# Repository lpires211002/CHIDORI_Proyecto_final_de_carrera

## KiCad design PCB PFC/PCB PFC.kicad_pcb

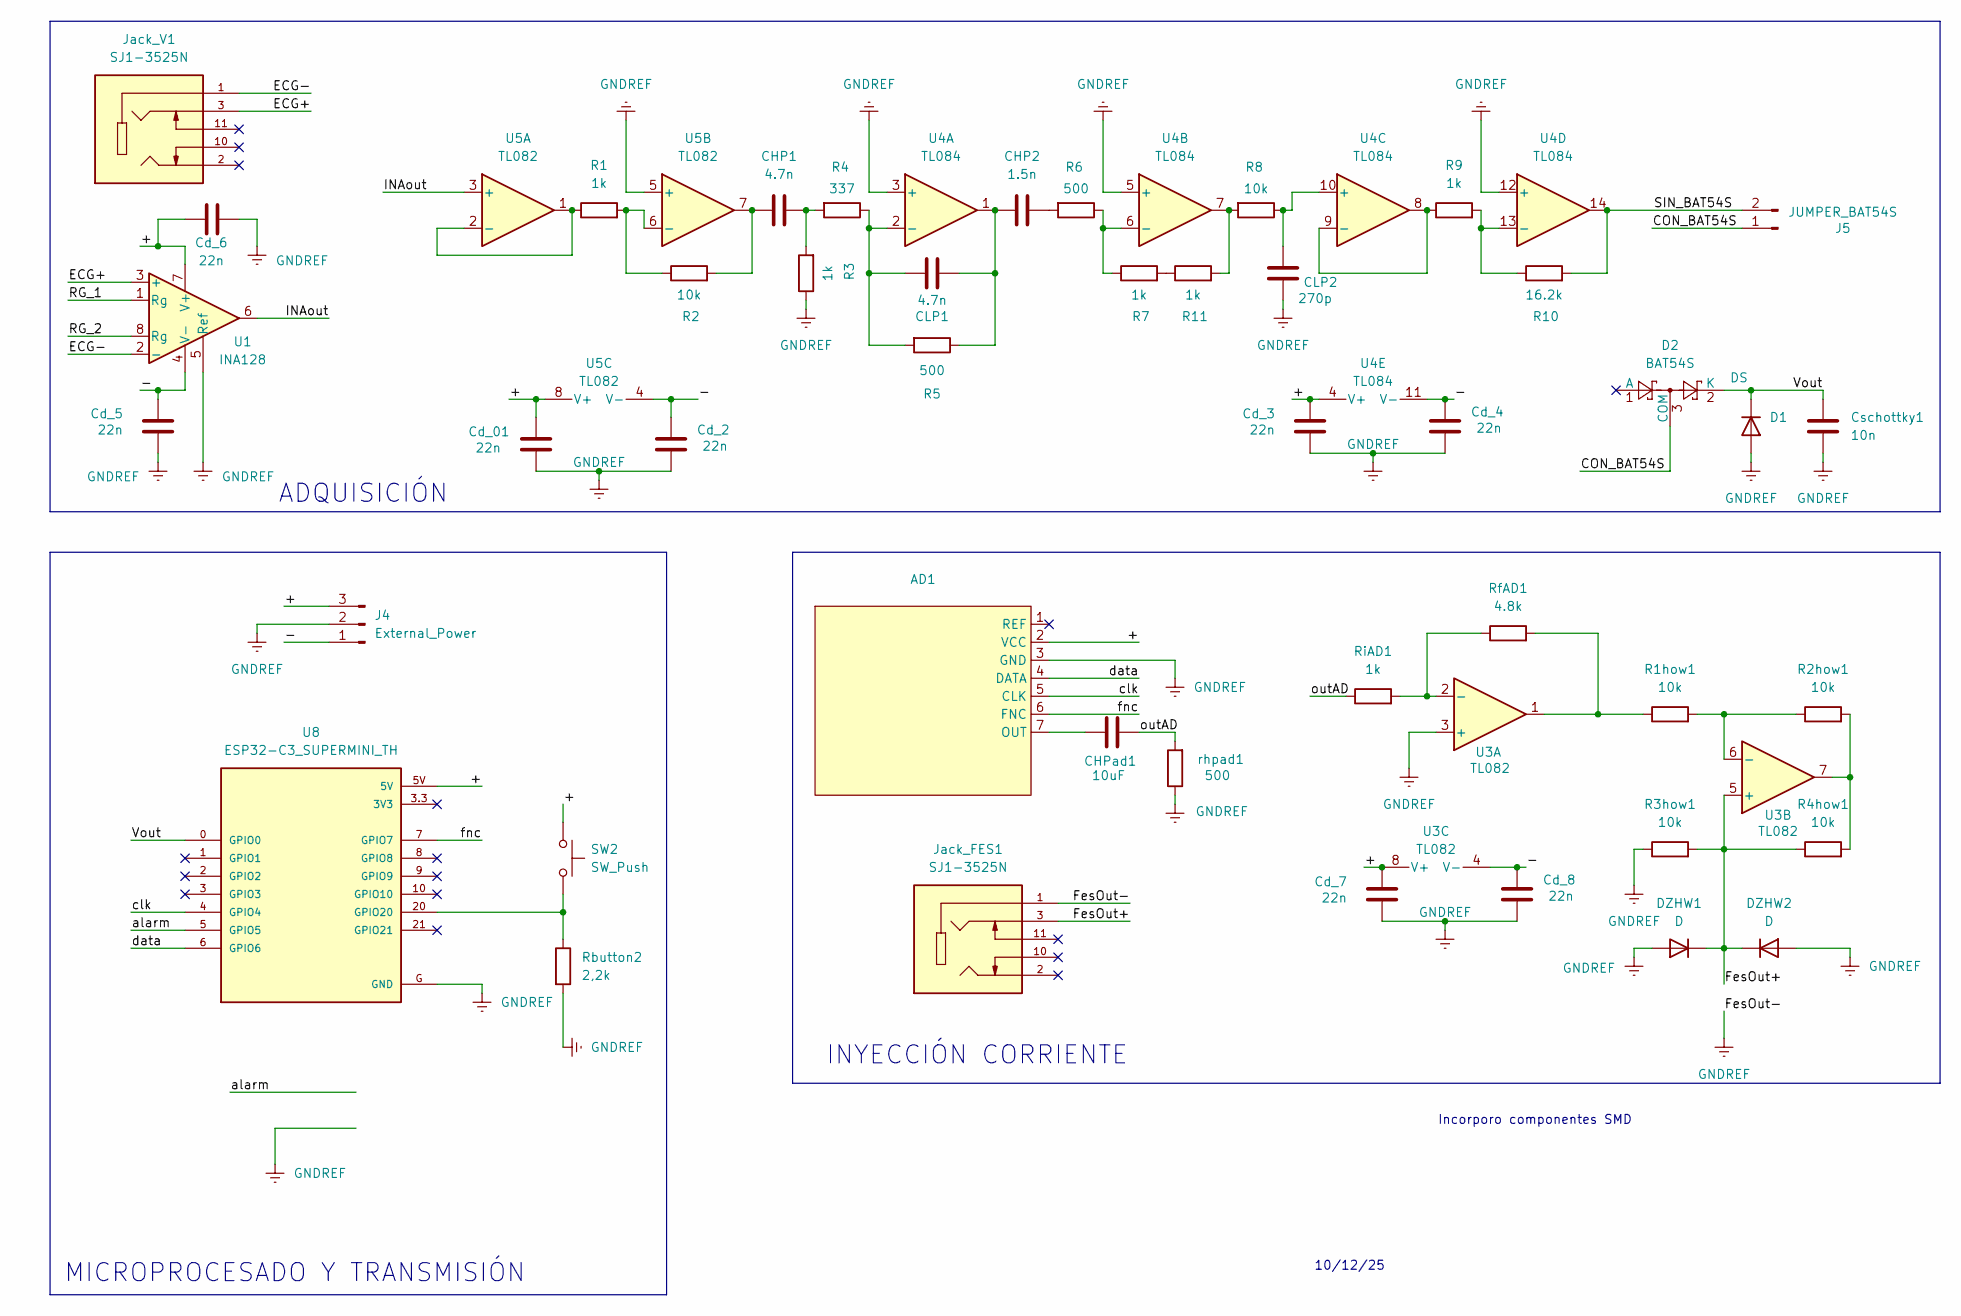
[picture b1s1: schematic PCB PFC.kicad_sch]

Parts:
AD1: AD9833
CHP1: 4.7n; C_0603_1608Metric
CHP2: 1.5n; C_0603_1608Metric
CHPad1: 10uF; C_0603_1608Metric
CLP1: 4.7n; C_0603_1608Metric
CLP2: 270p; C_0603_1608Metric
Cd_01, Cd_2, Cd_3, Cd_4, Cd_5, Cd_6, Cd_7, Cd_8: 22n; C_0603_1608Metric
Cschottky1: 10n; C_0603_1608Metric
D1: DS; D_DO-35_SOD27_P7.62mm_Horizontal
D2: BAT54S; SOT-23
DZHW1, DZHW2: D; D_DO-35_SOD27_P7.62mm_Horizontal
J4: External_Power; JST_EH_B3B-EH-A_1x03_P2.50mm_Vertical
J5: JUMPER_BAT54S; PinSocket_1x02_P2.54mm_Vertical
Jack_FES1: SJ1-3525N; CUI_SJ1-3525N; PARTREV 1.05
Jack_V1: SJ1-3525N; CUI_SJ1-3525N; PARTREV 1.05
R1, R3, R7, R9, R11: 1k; R_0805_2012Metric
R1how1, R2, R2how1, R3how1, R4how1, R8: 10k; R_0805_2012Metric
R4: 337; R_0805_2012Metric
R5, R6: 500; R_0805_2012Metric
R10: 16.2k; R_0805_2012Metric
Rbutton2: 2,2k; R_0805_2012Metric
RfAD1: 4.8k; R_0805_2012Metric
RiAD1: 1k; R_0805_2012Metric
SW2: SW_Push; SW_PUSH_6mm
U1: INA128; SOIC-8_3.9x4.9mm_P1.27mm
U3, U5: TL082; SOIC-8_3.9x4.9mm_P1.27mm
U4: TL084; SOIC-14_3.9x8.7mm_P1.27mm
U8: ESP32-C3_SUPERMINI_TH; MODULE_ESP32-C3_SUPERMINI_TH
rhpad1: 500; R_0805_2012Metric

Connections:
/+: AD1.2 (VCC), Cd_01.2, Cd_3.2, Cd_6.2, Cd_7.2, J4.3, SW2.1, U1.7 (V+), U3.8 (V+), U4.4 (V+), U5.8 (V+), U8.5V
/-: Cd_2.2, Cd_4.2, Cd_5.2, Cd_8.2, J4.1, U1.4 (V-), U3.4 (V-), U4.11 (V-), U5.4 (V-)
/CON_BAT54S: D2.3 (COM), J5.1
/ECG+: Jack_V1.3, U1.3 (+)
/ECG-: Jack_V1.1, U1.2 (-)
/FesOut+: DZHW1.1 (K), DZHW2.1 (K), Jack_FES1.3, R3how1.2, R4how1.1, U3.5 (+)
/INAout: U1.6, U5.3 (+)
/RG_1: U1.1 (Rg)
/RG_2: U1.8 (Rg)
/SIN_BAT54S: J5.2, R10.2, U4.14
/Vout: Cschottky1.2, D1.1 (K), D2.2 (K), U8.0 (GPIO0)
/alarm: U8.5 (GPIO5); also elsewhere on the board
/clk: AD1.5 (CLK), U8.4 (GPIO4)
/data: AD1.4 (DATA), U8.6 (GPIO6)
/fnc: AD1.6 (FNC), U8.7 (GPIO7)
/outAD: CHPad1.2, RiAD1.1, rhpad1.2
GNDREF: AD1.3 (GND), CLP2.1, Cd_01.1, Cd_2.1, Cd_3.1, Cd_4.1, Cd_5.1, Cd_6.1, Cd_7.1, Cd_8.1, Cschottky1.1, D1.2 (A), DZHW1.2 (A), DZHW2.2 (A), J4.2, Jack_FES1.1, R3.1, R3how1.1, Rbutton2.2, U1.5 (Ref), U3.3 (+), U4.3 (+), U4.5 (+), U4.12 (+), U5.5 (+), U8.G (GND), rhpad1.1; also elsewhere on the board
unnamed: AD1.7 (OUT), CHPad1.1
unnamed: CHP1.1, R2.2, U5.7
unnamed: CHP1.2, R3.2, R4.2
unnamed: CHP2.1, CLP1.2, R5.1, U4.1
unnamed: CHP2.2, R6.2
unnamed: R1how1.1, RfAD1.2, U3.1
unnamed: R2how1.2, R4how1.2, U3.7
unnamed: R7.2, R11.1
unnamed: R8.2, R11.2, U4.7
unnamed: RfAD1.1, RiAD1.2, U3.2 (-)
unnamed: R1how1.2, R2how1.1, U3.6 (-)
unnamed: CLP1.1, R4.1, R5.2, U4.2 (-)
unnamed: R6.1, R7.1, U4.6 (-)
unnamed: CLP2.2, R8.1, U4.10 (+)
unnamed: R9.1, U4.8, U4.9 (-)
unnamed: R9.2, R10.1, U4.13 (-)
unnamed: R1.1, U5.1, U5.2 (-)
unnamed: R1.2, R2.1, U5.6 (-)
unnamed: Rbutton2.1, SW2.2, U8.20 (GPIO20)

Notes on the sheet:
10/12/25
ADQUISICIÓN
Incorporo componentes SMD
MICROPROCESADO Y TRANSMISIÓN
INYECCIÓN CORRIENTE

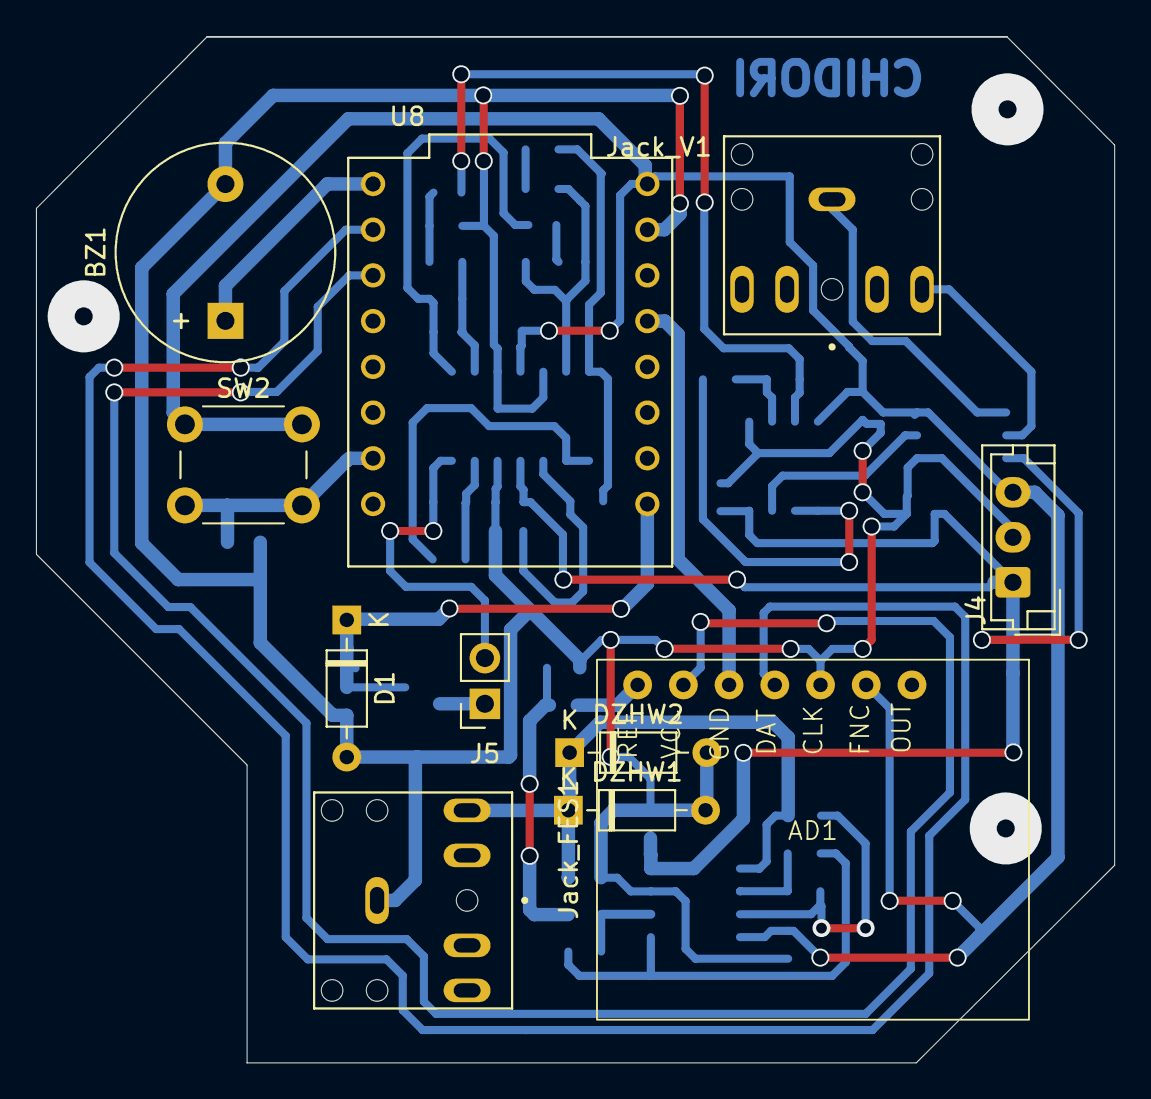
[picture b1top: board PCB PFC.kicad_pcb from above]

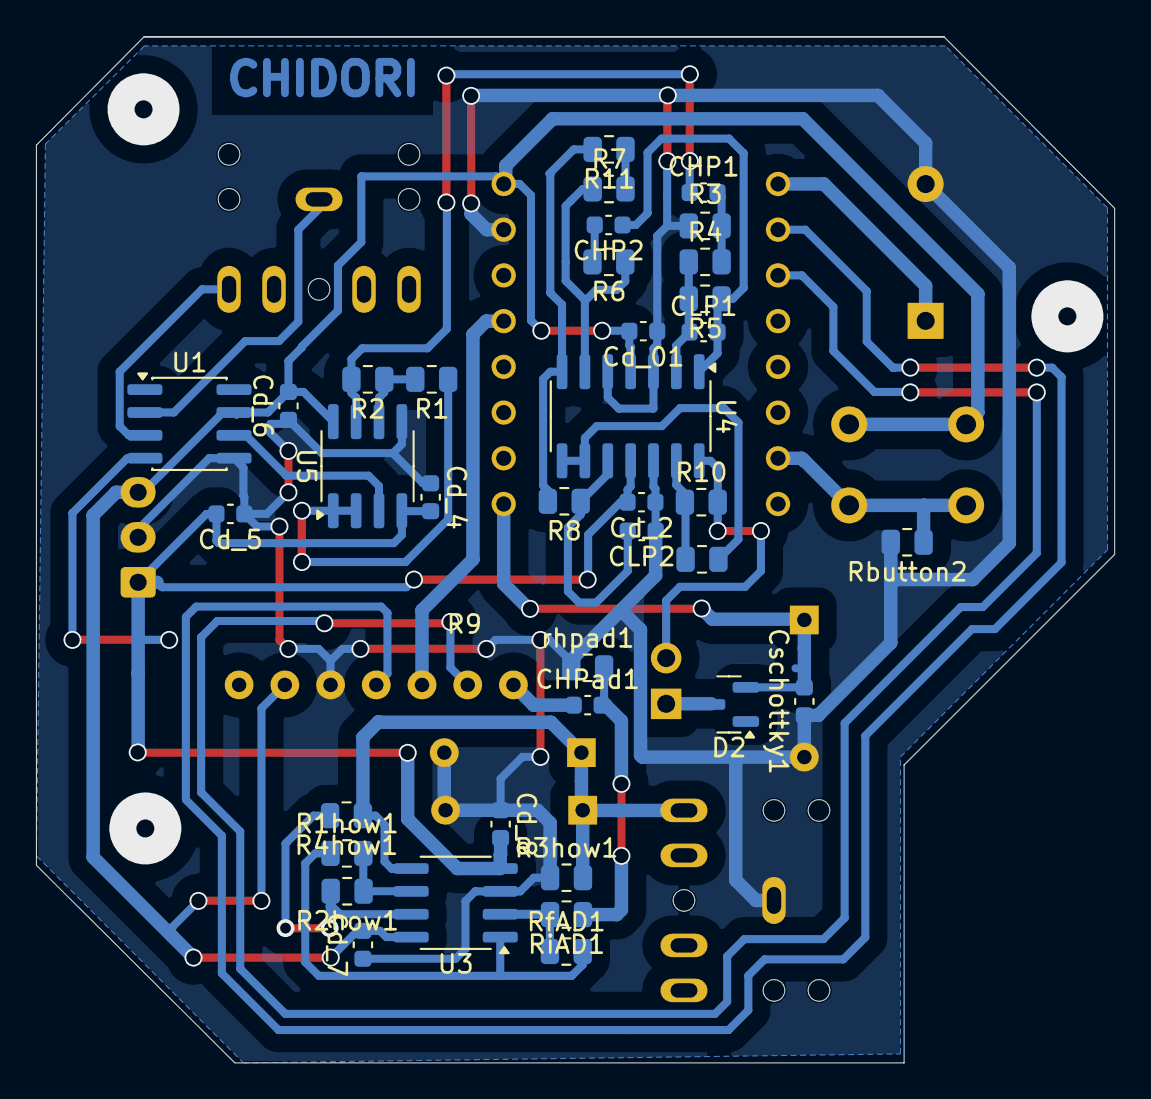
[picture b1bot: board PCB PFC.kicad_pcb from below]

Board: 2 copper layers, 59.9 x 57.0 mm, 48 parts (37 on the bottom side), 34 nets.

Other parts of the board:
BZ1: Buzzer; Buzzer_12x9.5RM7.6

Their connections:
/alarm: BZ1.1 (+); also elsewhere on the board
GNDREF: BZ1.2 (-); also elsewhere on the board

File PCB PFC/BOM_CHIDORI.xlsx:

# | Designadores | Cant. | Valor | Footprint | MPN sugerido (CONFIRMAR) | Notas
1 | CLP1 | 1 | 100p | C_0603 | Samsung CL10C101JB8NNNC | C0G/NP0 50V
2 | CLP2 | 1 | 270p | C_0603 | Samsung CL10C271JB8NNNC | C0G/NP0 50V
3 | CHP2 | 1 | 1.5n | C_0603 | Samsung CL10B152KB8NNNC | X7R 50V
4 | CHP1,Cschottky1 | 2 | 4.7n | C_0603 | Samsung CL10B472KB8NNNC | X7R 50V
5 | Cd_01,Cd_2,Cd_4,Cd_5,Cd_6,Cd_7,Cd_8 | 7 | 22n | C_0603 | Samsung CL10B223KB8NNNC | X7R 50V
6 | CHPad1 | 1 | 10uF | C_0603 | Samsung CL10A106KP8NNNC | X5R - confirmar tension >= alimentacion
7 | R1,R11,R3,R4,R7,R9,RiAD1 | 7 | 1k | R_0805 | Yageo RC0805FR-071KL | 1% 1/8W
8 | R1how1,R2,R2how1,R3how1,R4how1,R8 | 6 | 10k | R_0805 | Yageo RC0805FR-0710KL | 1% 1/8W
9 | Rbutton2 | 1 | 2.2k | R_0805 | Yageo RC0805FR-072K2L | 1% 1/8W
10 | R5 | 1 | 22k | R_0805 | Yageo RC0805FR-0722KL | 1% 1/8W
11 | R10 | 1 | 4.7k | R_0805 | Yageo RC0805FR-074K7L | 1% 1/8W
12 | RfAD1 | 1 | 4.8k | R_0805 | RC0805FR-074K75L (4.75k) | VALOR RARO: 4.8k no existe. Confirmar 4.7k o 4.75k
13 | R6,rhpad1 | 2 | 500 | R_0805 | RC0805FR-07499RL (499R) | VALOR RARO: 500 no estandar. Usar 499R o 510R
14 | U1 | 1 | INA128 | SOIC-8 | TI INA128UA (o INA128U/2K5) | Inst. amp - confirmar MPN exacto
15 | U3,U5 | 2 | TL082 | SOIC-8 | TI TL082CDR | Op-amp dual
16 | U4 | 1 | TL084 | SOIC-14 | TI TL084CDR | Op-amp cuadruple
17 | D2 | 1 | BAT54S | SOT-23 | Diodes BAT54S-7-F | Schottky dual
 | TOTAL | 37

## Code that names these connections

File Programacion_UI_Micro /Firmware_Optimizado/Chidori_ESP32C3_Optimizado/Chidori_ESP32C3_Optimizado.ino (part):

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// ║     Partition Scheme: Default 4MB with spiffs                ║
// ║                                                              ║
// ║  Si "USB CDC On Boot" NO está en Enabled, los pines 20 y 21 ║
// ║  son tomados por el UART0 (Serial) y el BOTÓN (GPIO20)       ║
// ║  dejará de funcionar.                                        ║
// ╚══════════════════════════════════════════════════════════════╝
//
// Asignación de pines (verificada contra esquemático KiCAD):
//   GPIO 0  → ADC (Vout, salida del detector Schottky)
//   GPIO 4  → SPI SCK   (clk del AD9833)
//   GPIO 5  → BUZZER    (alarm)
//   GPIO 6  → SPI MOSI  (data del AD9833)
//   GPIO 7  → SPI FSYNC (fnc del AD9833)
//   GPIO 20 → BOTÓN     (SW2, pull-down 2.2k → activo en HIGH)
//
// ─────────────────────────────────────────────────────────────────
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#include <math.h>

/* ================= ASIGNACIÓN DE PINES (ver esquemático) ================= */
#define BUZZER       5    // GPIO5  → buzzer (alarm)
#define BUTTON      20    // GPIO20 → botón SW2 (pull-down externo 2.2k)
#define ADC_PIN      0    // GPIO0  → entrada ADC (Vout del detector Schottky)
#define PIN_MOSI     6    // GPIO6  → SPI MOSI (data del AD9833)
#define PIN_SCK      4    // GPIO4  → SPI SCK  (clk del AD9833)
#define PIN_FSYNC    7    // GPIO7  → SPI FSYNC (fnc del AD9833, CS manual)

/* ================= CONSTANTES ELÉCTRICAS DEL CIRCUITO ================= */
// Generador AD9833 (verificado contra esquemático: Rfad/Riad = 4.8k/1k = 4.8)
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
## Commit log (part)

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2025-11-12 Cambio repo por carpeta
2025-11-27 corrijo tema blanco no funcionan descargas
2025-11-28 gran mejora del js con claude
2025-11-28 corrijo descarga de .txt
2025-11-30 Agrego huellas y symbols de AD9833
2025-12-10 Cambio valores a comerciales y agrego OpAmps SMD
2025-12-18 Placa final chidori 3V3 by Gus
2025-12-18 Pruebas pfc con arduino
2026-03-24 Cambios en el filtrado
2026-04-01 pruebo capacitores schottky
2026-05-22 Cambio del filtrado actual, más ganancia y cambio de capa
2026-05-22 cambio de capa
2026-05-24 actualizacion de placa y filtrado: correccion de ad9833 e ina + filtrado
2026-05-24 feat: migración a React premium (UI_REACT) y firmware optimizado con mDNS y WebSocket central
2026-05-24 no se que onda
2026-05-24 feat: vejiga dinámica, asistente de calibración e integración con Supabase Cloud
2026-05-24 correccion del firm
2026-05-25 feat(motion): Sparklines en KPIs + MorphingDialog en fila de sesiones (21st.dev)
    - Sparkline component (SVG + motion.path con spring pathLength, head animado)
    - StatsGrid reusa buffer de RealTimeCharts (zHistory/rateHistory, ventana 40)
    - AdminView: motion.button con layoutId compartido row ↔ SessionDetailModal,
    LayoutGroup + AnimatePresence para morph fluído al abrir/cerrar
2026-06-04 algo
2026-06-10 feat(firmware): WiFiManager edición robusta · transmisión en tiempo real confiable
    - Heartbeat WS 15s/3s/2: purga clientes fantasma que frenaban broadcastTXT
    - Reconexión WiFi runtime no bloqueante con backoff 5-30s + reboot preventivo
    - TX power 8.5 dBm (fix antena C3 Super Mini + brown-out USB CDC)
    - AD9833 init antes del WiFi + re-init defensivo en cada START
    - Scheduler de muestreo sin ráfagas (re-sync si el loop se atrasa)
    - Sin String en camino crítico (snprintf) · diagnóstico cada 10s + cmd STATUS/PING
2026-06-11 feat(ui): rediseño v3 + lectura robusta congruente con firmware + roles admin
    Dashboard:
    - Arquitectura nueva: header mínimo con menú ⋯, barra de comando
    (control primario + cronómetro), grid de monitoreo con vejiga hero
    y resumen de alarma, setup en tabs Configuración/Eventos.
    - Gráficos fusionados en una card con toggle Impedancia/dZdt.
    - Readout jerárquico de 3 celdas (hero + basal + tasa).
2026-06-11 fix(ui): hardening post-assessment · updaters puros, decimación, backup anti-F5, watchdog de señal
    - handleIncomingData: tasa calculada sobre buffers ref síncronos, fuera de
    los updaters de setState (StrictMode duplicaba puntos en rateData).
    - Decimación LTTB en el gráfico (Chart.js decimation, 500 muestras sobre
    1000 puntos): sesiones de horas sin degradar el render; dataset completo
    intacto para export y cloud commit.
    - Backup de sesión a localStorage cada 30 s midiendo + al pausar; banner
2026-06-26 Placa actualizada
